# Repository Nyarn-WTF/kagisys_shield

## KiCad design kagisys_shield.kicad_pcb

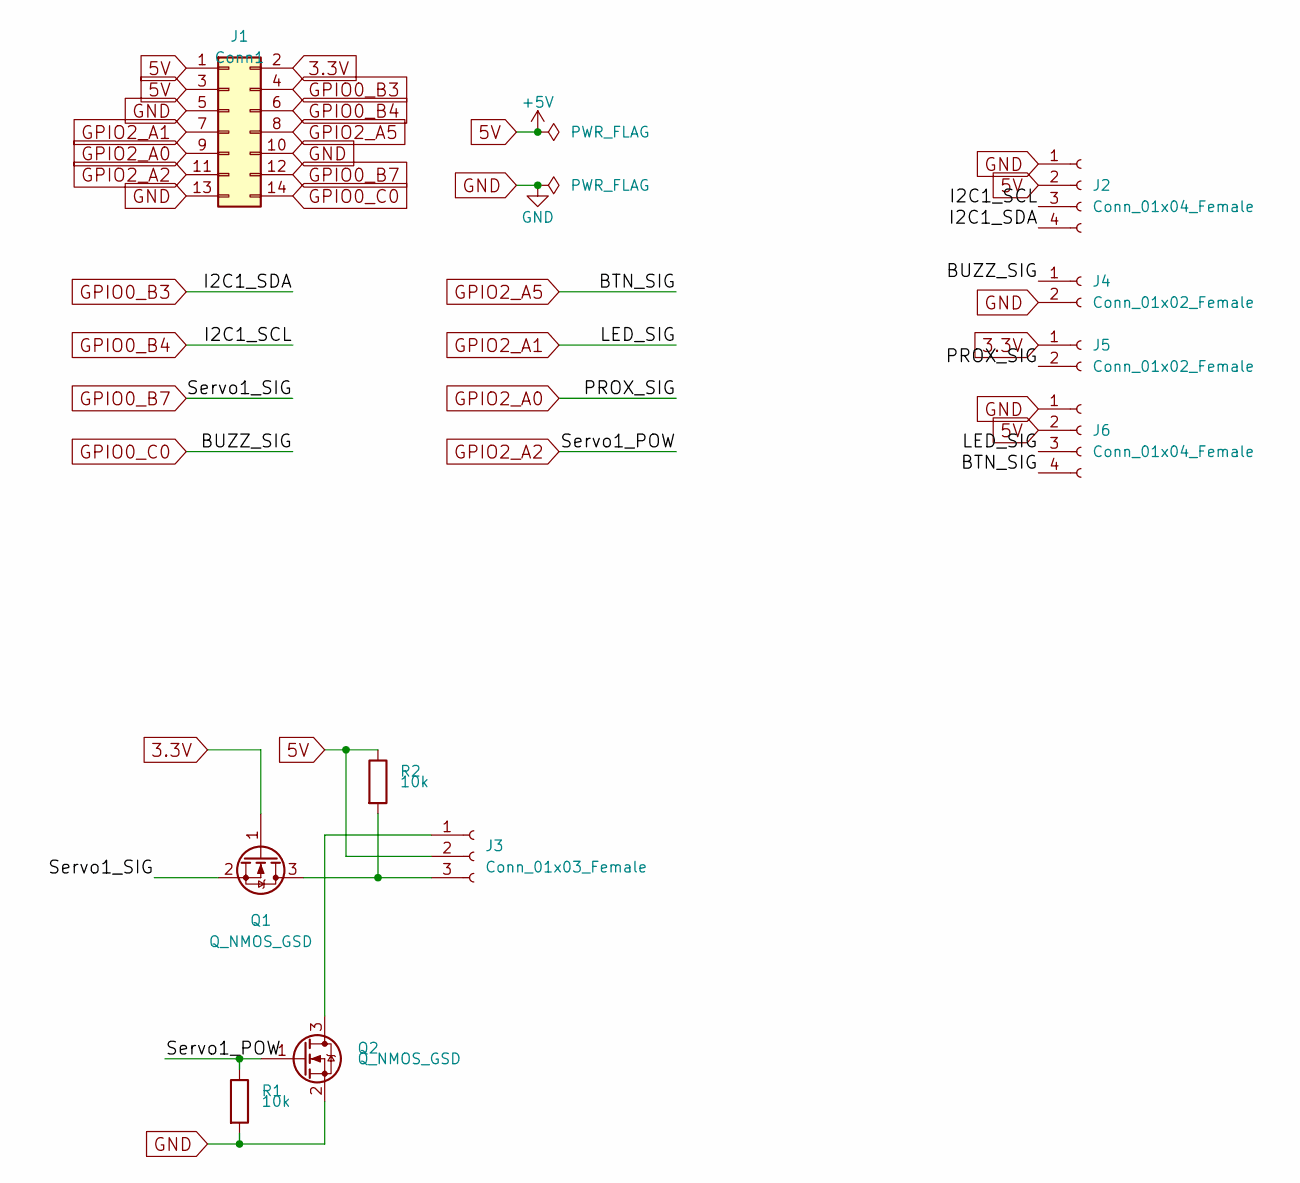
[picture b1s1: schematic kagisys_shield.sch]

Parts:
J1: Conn1; PinHeader_2x07_P2.54mm_Horizontal
J2, J6: Conn_01x04_Female; PinSocket_1x04_P2.54mm_Horizontal
J3: Conn_01x03_Female; PinSocket_1x03_P2.54mm_Horizontal
J4, J5: Conn_01x02_Female; PinSocket_1x02_P2.54mm_Horizontal
Q1, Q2: Q_NMOS_GSD; SOT-23
R1, R2: 10k; R_Axial_DIN0309_L9.0mm_D3.2mm_P12.70mm_Horizontal

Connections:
3.3V: J1.2, J5.1, Q1.1 (G)
5V: J1.1, J1.3, J2.2, J3.2, J6.2, R2.1
GND: J1.5, J1.10, J1.13, J2.1, J4.2, J6.1, Q2.2 (S), R1.2
GPIO0_B3: J1.4, J2.4
GPIO0_B4: J1.6, J2.3
GPIO0_B7: J1.12, Q1.2 (S)
GPIO0_C0: J1.14, J4.1
GPIO2_A0: J1.9, J5.2
GPIO2_A1: J1.7, J6.3
GPIO2_A2: J1.11, Q2.1 (G), R1.1
GPIO2_A5: J1.8, J6.4
unnamed: J3.1, Q2.3 (D)
unnamed: J3.3, Q1.3 (D), R2.2

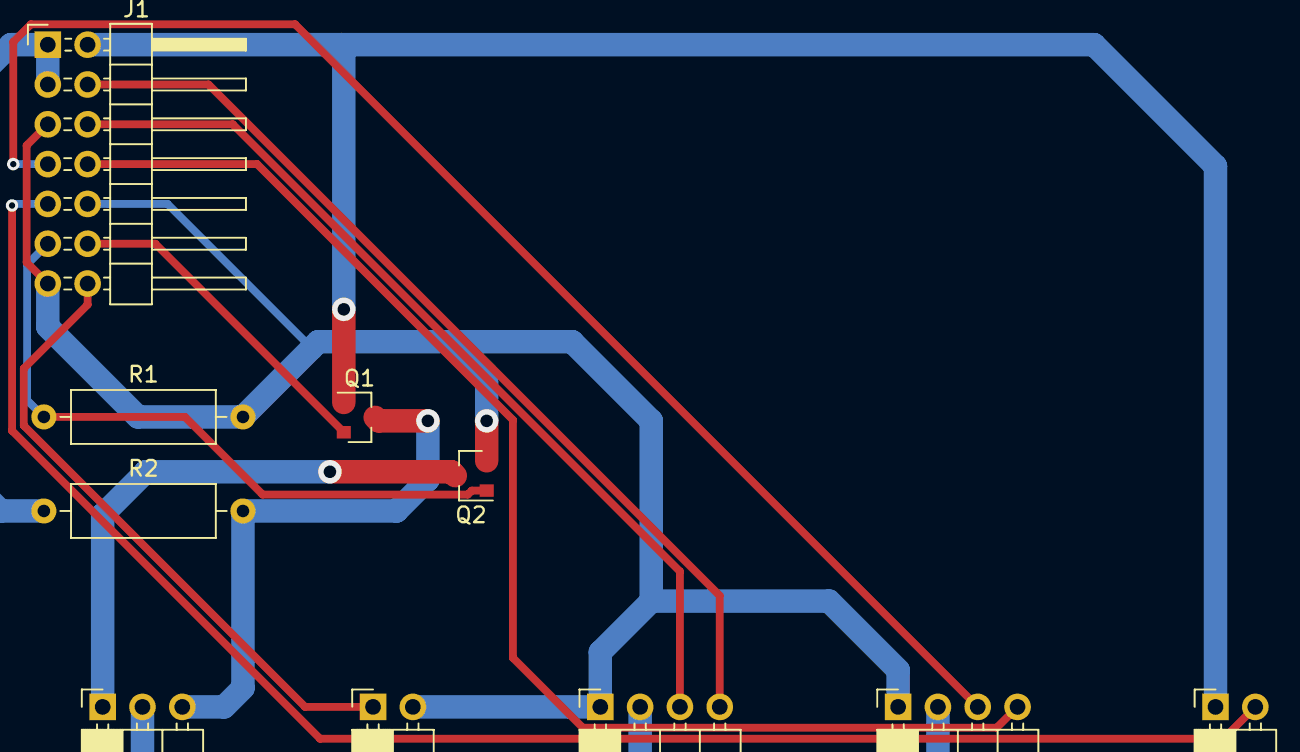
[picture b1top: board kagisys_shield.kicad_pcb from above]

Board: 2 copper layers, 10 parts (0 on the bottom side), 13 nets.

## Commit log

2019-08-19 rename
2019-08-19 reset
2019-08-19 add conn1
2019-08-19 fix pin_layout
2019-08-19 add footprint of pinheader
2019-08-19 add powerflag
2019-08-20 fix pcb
2019-08-22 add gbr
